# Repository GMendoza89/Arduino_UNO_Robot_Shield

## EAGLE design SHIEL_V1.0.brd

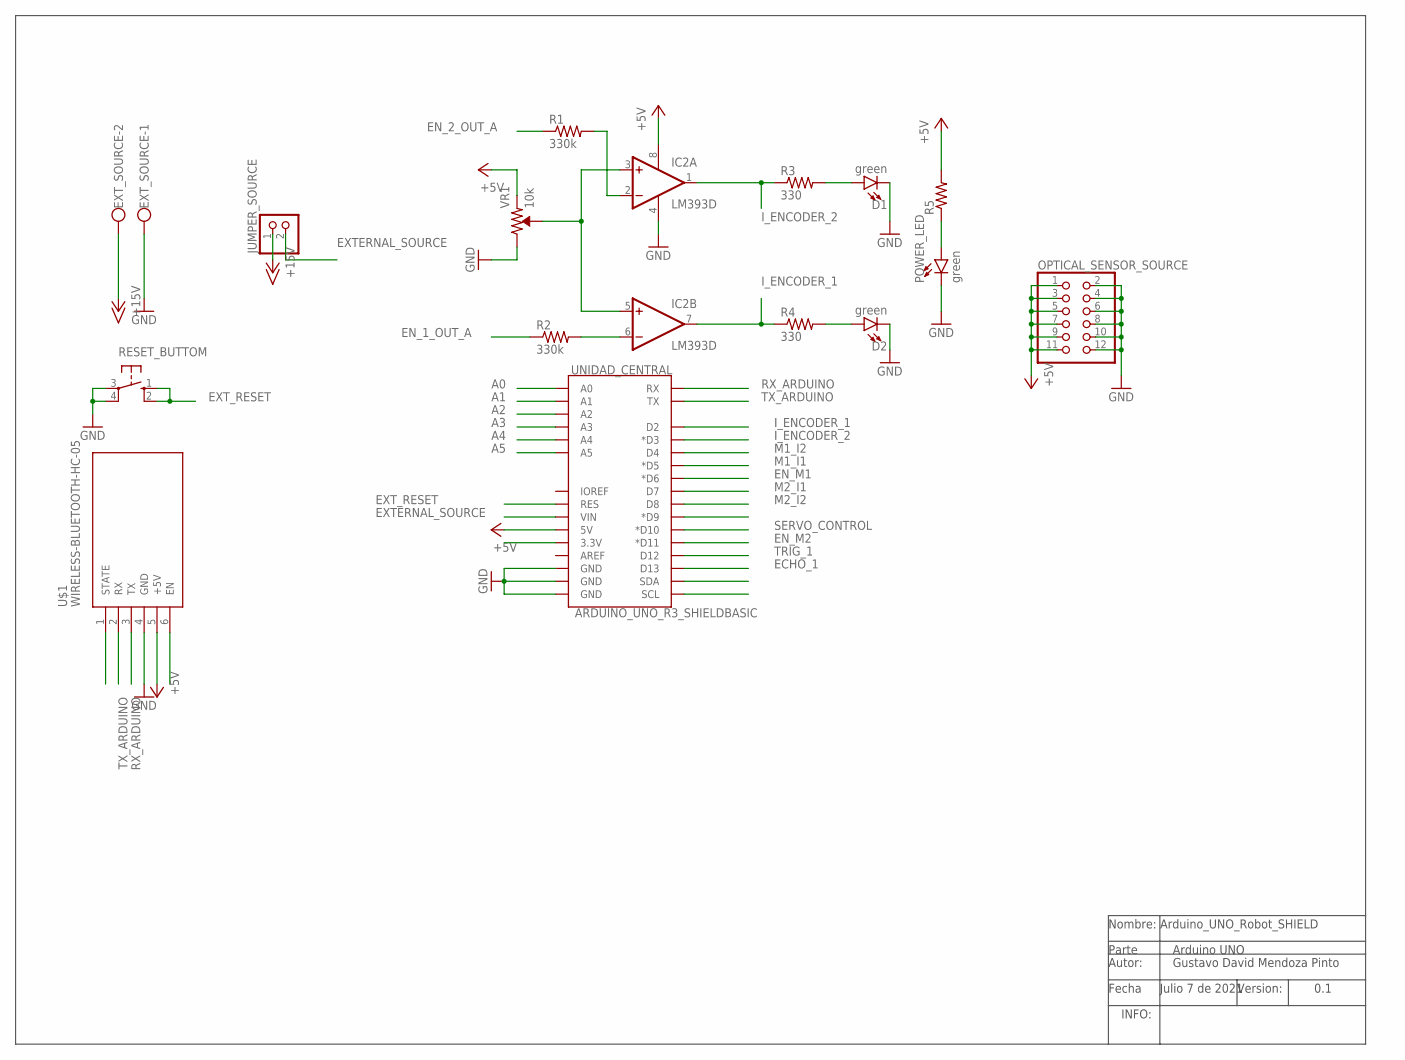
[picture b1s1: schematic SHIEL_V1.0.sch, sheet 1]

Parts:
D1, D2: green; LED_3MM-NS
EXT_SOURCE: W237-102
IC2: LM393D; SO08
JUMPER_SOURCE: PINHD-1X2; 1X02
OPTICAL_SENSOR_SOURCE: PINHD-2X6; 2X06
POWER_LED: green; LED_3MM-NS
R1, R2: 330k; M2012
R3, R4: 330; M2012
R5: R-US_M2012; M2012
RESET_BUTTOM: 10-XX; B3F-10XX
U$1: WIRELESS-BLUETOOTH-HC-05
UNIDAD_CENTRAL: ARDUINO_UNO_R3_SHIELDBASIC; UNO_R3_SHIELD
VR1: 10k; TRIMPOT-PTH-3386U

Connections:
+5V: IC2.8 (V+), OPTICAL_SENSOR_SOURCE.1, OPTICAL_SENSOR_SOURCE.3, OPTICAL_SENSOR_SOURCE.5, OPTICAL_SENSOR_SOURCE.7, OPTICAL_SENSOR_SOURCE.9, OPTICAL_SENSOR_SOURCE.11, R5.2, U$1.5 (+5V), UNIDAD_CENTRAL.5V, VR1.1 (CCW); also elsewhere on the board
+15V: EXT_SOURCE.2, JUMPER_SOURCE.1
A0: UNIDAD_CENTRAL.A0; also elsewhere on the board
A1: UNIDAD_CENTRAL.A1; also elsewhere on the board
A2: UNIDAD_CENTRAL.A2; also elsewhere on the board
A3: UNIDAD_CENTRAL.A3; also elsewhere on the board
A4: UNIDAD_CENTRAL.A4; also elsewhere on the board
A5: UNIDAD_CENTRAL.A5; also elsewhere on the board
ECHO_1: UNIDAD_CENTRAL.D13; also elsewhere on the board
EN_1_OUT_A: R2.1; also elsewhere on the board
EN_2_OUT_A: R1.1; also elsewhere on the board
EN_M1: UNIDAD_CENTRAL.D6 (*D6); also elsewhere on the board
EN_M2: UNIDAD_CENTRAL.D11 (*D11); also elsewhere on the board
EXTERNAL_SOURCE: JUMPER_SOURCE.2, UNIDAD_CENTRAL.VIN; also elsewhere on the board
EXT_RESET: RESET_BUTTOM.1 (S), RESET_BUTTOM.2 (S1), UNIDAD_CENTRAL.RES
GND: D1.K (C), D2.K (C), EXT_SOURCE.1, IC2.4 (V-), OPTICAL_SENSOR_SOURCE.2, OPTICAL_SENSOR_SOURCE.4, OPTICAL_SENSOR_SOURCE.6, OPTICAL_SENSOR_SOURCE.8, OPTICAL_SENSOR_SOURCE.10, OPTICAL_SENSOR_SOURCE.12, POWER_LED.K (C), RESET_BUTTOM.3, RESET_BUTTOM.4 (P1), U$1.4 (GND), UNIDAD_CENTRAL.GND@0 (GND), UNIDAD_CENTRAL.GND@1 (GND), UNIDAD_CENTRAL.GND@2 (GND), VR1.3 (CW); also elsewhere on the board
I_ENCODER_1: IC2.7 (OUT), R4.1, UNIDAD_CENTRAL.D2; also elsewhere on the board
I_ENCODER_2: IC2.1 (OUT), R3.1, UNIDAD_CENTRAL.D3 (*D3); also elsewhere on the board
M1_I1: UNIDAD_CENTRAL.D5 (*D5); also elsewhere on the board
M1_I2: UNIDAD_CENTRAL.D4; also elsewhere on the board
M2_I1: UNIDAD_CENTRAL.D7; also elsewhere on the board
M2_I2: UNIDAD_CENTRAL.D8; also elsewhere on the board
unnamed: IC2.3 (+IN), IC2.5 (+IN), VR1.2 (WIPER)
unnamed: IC2.2 (-IN), R1.2
unnamed: IC2.6 (-IN), R2.2
unnamed: POWER_LED.A, R5.1
unnamed: D1.A, R3.2
unnamed: D2.A, R4.2
RX_ARDUINO: U$1.3 (TX), UNIDAD_CENTRAL.RX
SERVO_CONTROL: UNIDAD_CENTRAL.D10 (*D10); also elsewhere on the board
TRIG_1: UNIDAD_CENTRAL.D12; also elsewhere on the board
TX_ARDUINO: U$1.2 (RX), UNIDAD_CENTRAL.TX

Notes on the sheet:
Nombre: Arduino_UNO_Robot_SHIELD
Autor:
Version:
Fecha
INFO:
Parte
Arduino UNO
Gustavo David Mendoza Pinto
Julio 7 de 2021
0.1

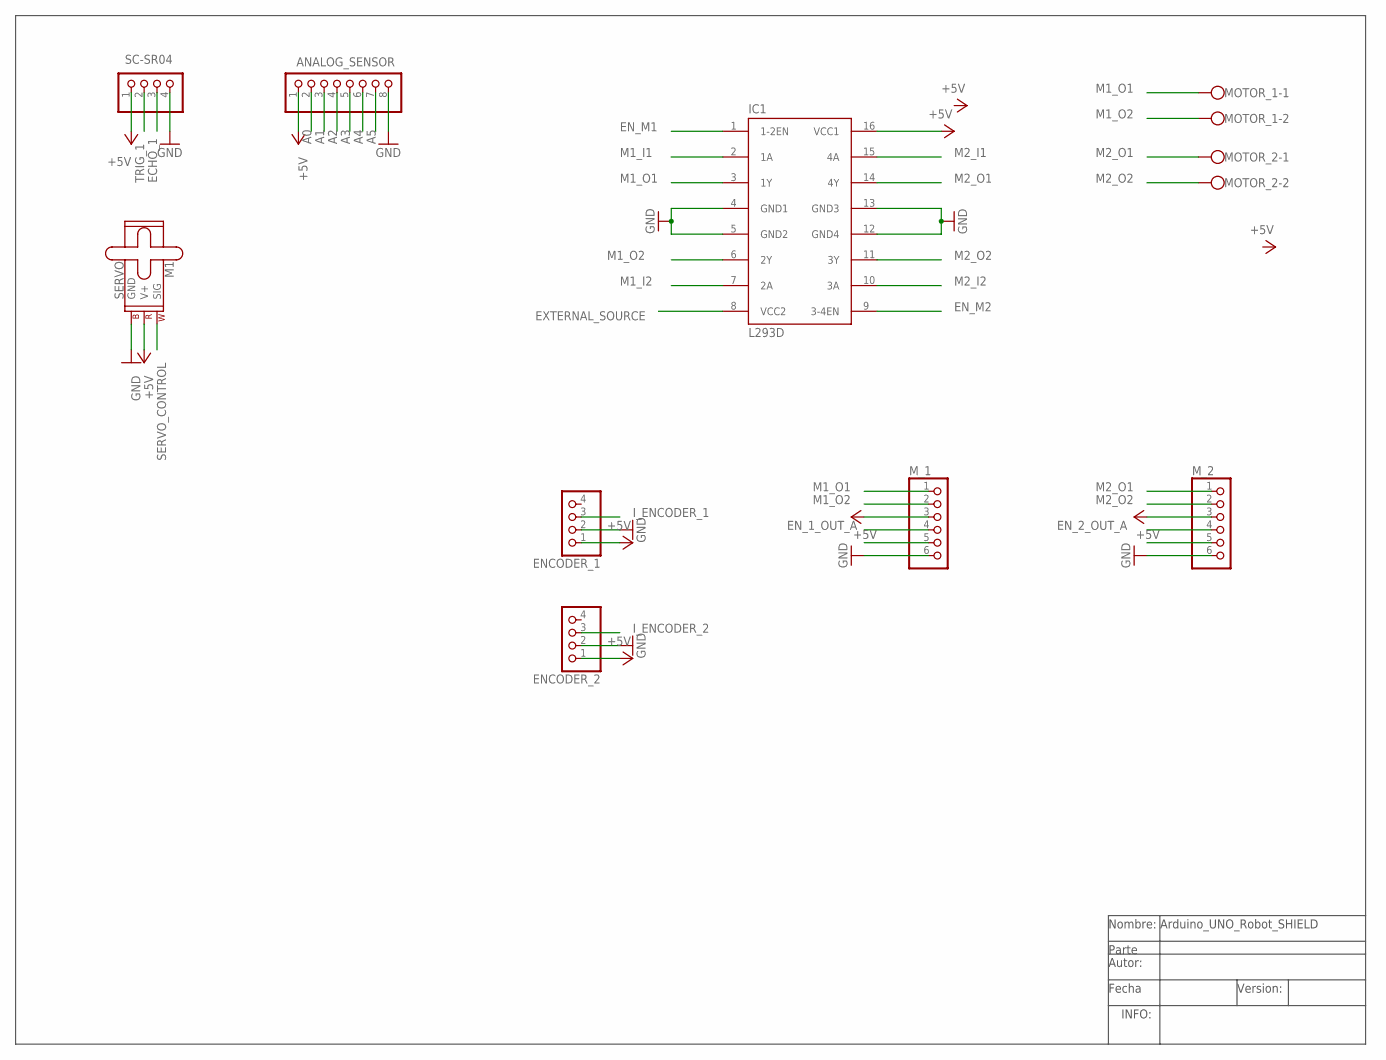
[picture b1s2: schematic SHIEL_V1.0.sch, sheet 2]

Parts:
ANALOG_SENSOR: PINHD-1X8; 1X08
ENCODER_1, ENCODER_2: PINHD-1X4; 1X04
IC1: L293D; DIL16
M1: SERVO; 1X03
MOTOR_1, MOTOR_2: W237-102
M_1, M_2: PINHD-1X6; 1X06
SC-SR04: PINHD-1X4; 1X04

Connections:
+5V: ANALOG_SENSOR.1, ENCODER_1.1, ENCODER_2.1, IC1.16 (VCC1), M1.2 (V+), M_1.3, M_2.3, SC-SR04.1; also elsewhere on the board
A0: ANALOG_SENSOR.2; also elsewhere on the board
A1: ANALOG_SENSOR.3; also elsewhere on the board
A2: ANALOG_SENSOR.4; also elsewhere on the board
A3: ANALOG_SENSOR.5; also elsewhere on the board
A4: ANALOG_SENSOR.6; also elsewhere on the board
A5: ANALOG_SENSOR.7; also elsewhere on the board
ECHO_1: SC-SR04.3; also elsewhere on the board
EN_1_OUT_A: M_1.4; also elsewhere on the board
EN_2_OUT_A: M_2.4; also elsewhere on the board
EN_M1: IC1.1 (1-2EN); also elsewhere on the board
EN_M2: IC1.9 (3-4EN); also elsewhere on the board
EXTERNAL_SOURCE: IC1.8 (VCC2); also elsewhere on the board
GND: ANALOG_SENSOR.8, ENCODER_1.2, ENCODER_2.2, IC1.4 (GND1), IC1.5 (GND2), IC1.12 (GND4), IC1.13 (GND3), M1.3 (GND), M_1.6, M_2.6, SC-SR04.4; also elsewhere on the board
I_ENCODER_1: ENCODER_1.3; also elsewhere on the board
I_ENCODER_2: ENCODER_2.3; also elsewhere on the board
M1_I1: IC1.2 (1A); also elsewhere on the board
M1_I2: IC1.7 (2A); also elsewhere on the board
M1_O1: IC1.3 (1Y), MOTOR_1.1, M_1.1
M1_O2: IC1.6 (2Y), MOTOR_1.2, M_1.2
M2_I1: IC1.15 (4A); also elsewhere on the board
M2_I2: IC1.10 (3A); also elsewhere on the board
M2_O1: IC1.14 (4Y), MOTOR_2.1, M_2.1
M2_O2: IC1.11 (3Y), MOTOR_2.2, M_2.2
SERVO_CONTROL: M1.1 (SIG); also elsewhere on the board
TRIG_1: SC-SR04.2; also elsewhere on the board

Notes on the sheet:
Nombre: Arduino_UNO_Robot_SHIELD
Autor:
Version:
Fecha
INFO:
Parte

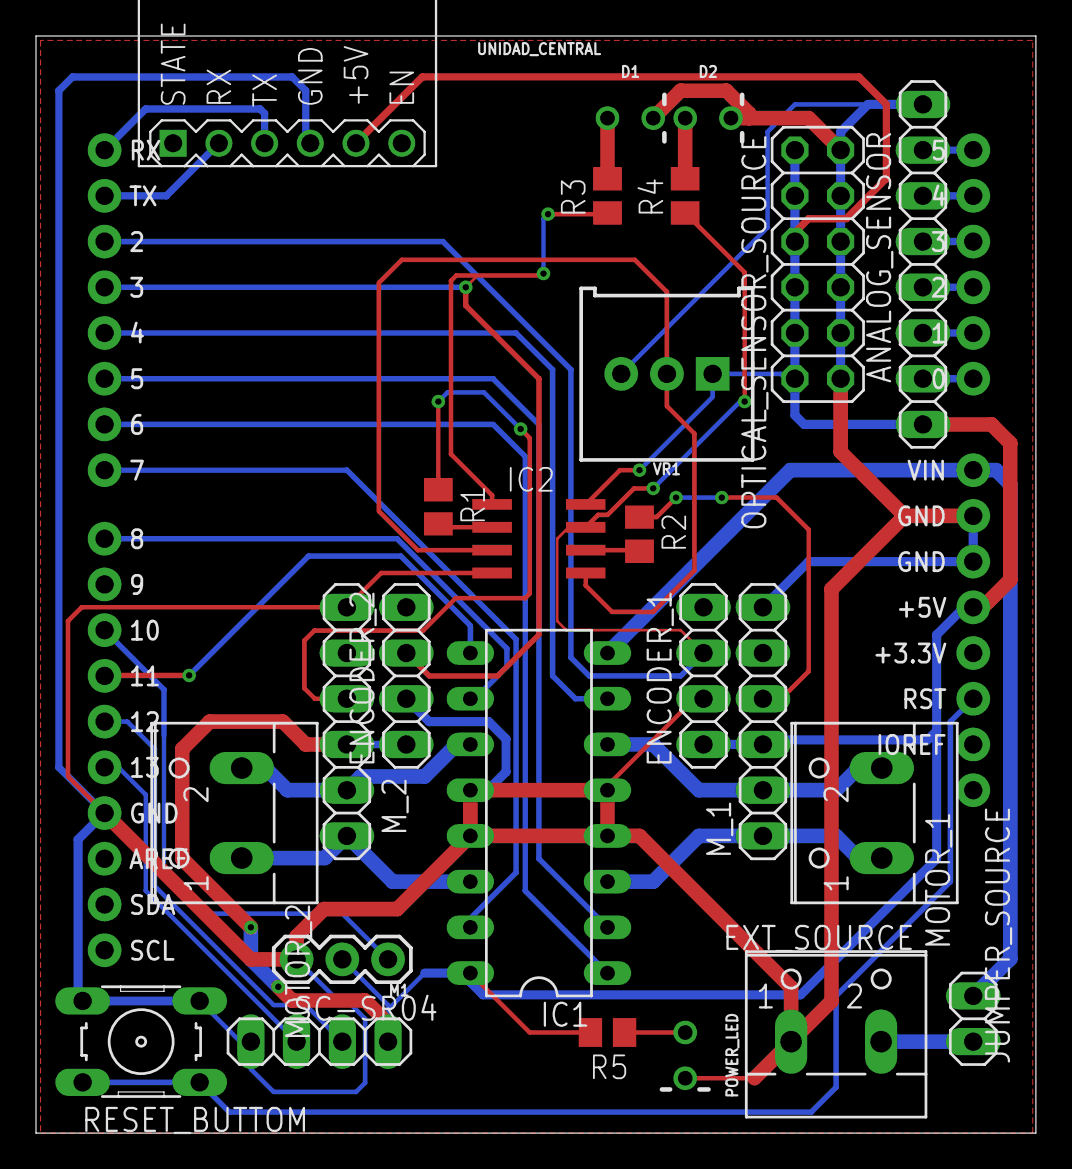
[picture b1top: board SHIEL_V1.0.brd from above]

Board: 2 copper layers, 55.5 x 61.0 mm, 26 parts (0 on the bottom side), 36 nets.

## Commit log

2022-12-06 Inicio de Repositorio
2022-12-06 Se incorpora esquemático
2022-12-06 Se incorpora el diseño del pcb
2022-12-06 Se agregan archivos de fabricación de pcb

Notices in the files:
parts and their libraries:
SparkFun-Boards: Licensing: Creative Commons ShareAlike 4.0 International - https://creativecommons.org/licenses/by-sa/4.0
diy-modules: Released under the Creative Commons Attribution 4.0 International License: http://creativecommons.org/licenses/by/4.0
